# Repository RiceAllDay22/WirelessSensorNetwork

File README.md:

# Introduction to the Wireless Sensor Network Project
This repository contains the files utilized to create a low-cost wireless sensor network to identify, locate, and quantify CO2 sources within an area. The primary component of the network is the CO2 Sensor Node, for which there are two variants: the Arduino Version and the XBee Version. 

Both variants have the same essential function of collecting CO2 and wind data. The difference, however, is that the Arduino Version stores data within a microSD card, while the XBee Version sends data to a central hub. The XBee Version is the prominent hardware of this project.

An external repository called the [CSR_Arduino_Collection](https://github.com/RiceAllDay22/CSR_Arduino_Collection) is a complementary project that contains guides, codes, schematics, and datasheets for operating various sensors and modules, including the ones used in WSN. 

The overall WSN project is divided into three sections. [Section 1](https://github.com/RiceAllDay22/WirelessSensorNetwork/tree/master/Section1-Prototyping) focuses on the development of the Sensor Nodes. Next, [Section 2](https://github.com/RiceAllDay22/WirelessSensorNetwork/tree/master/Section2-Networking) establishes a wireless network between active nodes. Finally, [Section 3](https://github.com/RiceAllDay22/WirelessSensorNetwork/tree/master/Section3-Detecting) uses the collected data to identify and locate possible CO2 sources. Below are summaries and highlights of each section. 

# [Section 1: Developing the Sensor Nodes](https://github.com/RiceAllDay22/WirelessSensorNetwork/tree/master/Section1-Prototyping)
The Sensor Nodes are the backbone of WSN. Although there are two different variants: the Arduino Version and the XBee Version, they all consist of a CO2 sensor, a wind anemometer, and a time-keeping module.

[Arduino Version](https://github.com/jkub6/WirelessSensorNetwork/tree/master/Section1-ArduinoVersion) 
- Microcontroller is Arduino Nano
- Data saved on to a local microSD card
- Hardware is built on a solderless breadboard
- Code is compiled using Arduino IDE <br>

[XBee Version](https://github.com/jkub6/WirelessSensorNetwork/tree/master/Section2-XBeeVersion)
- Microcontroller is Digi XBee3
- Data transmitted to central hub
- Hardware is assembled on a custom printed-cicuit board
- Code is compiled using PyCharm

## Overview of Sensor Node
- [Arduino Version](https://github.com/RiceAllDay22/WirelessSensorNetwork/tree/master/Section1-Prototyping/SensorNode-ArduinoVersion)
- [XBee Version](https://github.com/RiceAllDay22/WirelessSensorNetwork/tree/master/Section1-Prototyping/SensorNode-XBeeVersion)

## Assessments of Individual Components
- [CU1106 CO2 Sensor](https://github.com/RiceAllDay22/WirelessSensorNetwork/tree/master/Section1-Prototyping/Assessment-CU1106) (not used for in current Node iterations)
- [SCD30 CO2 Sensor](https://github.com/RiceAllDay22/WirelessSensorNetwork/tree/master/Section1-Prototyping/Assessment-SCD30) (currently implemented in both Node versions)
- [DS3231 Timekeeping Module](https://github.com/RiceAllDay22/WirelessSensorNetwork/tree/master/Section1-Prototyping/Assessment-DS3231) (currently implemented in both Node versions)

## Power Evaluations
- [Power Usage of Nodes](https://github.com/RiceAllDay22/WirelessSensorNetwork/tree/master/Section1-Prototyping/Evaluation-PowerUsage)
- [Solar Requirement](https://github.com/RiceAllDay22/WirelessSensorNetwork/tree/master/Section1-Prototyping/Evaluation-PowerUsage)

# [Section 2: Establishing the Network](https://github.com/RiceAllDay22/WirelessSensorNetwork/tree/master/Section2-Networking)

The board is designed using Autodesk Eagle.

# [Section 3: Locating Possible Carbon Sources](https://github.com/RiceAllDay22/WirelessSensorNetwork/tree/master/Section3-Detecting)
## Node Software
Code controlling individual nodes is compiled through the Arduino IDE.

Arduino Library Requirments:
 - RTClib
 - SdFat

resources:
[One Drive Resources Folder](https://uofutah-my.sharepoint.com/:f:/g/personal/u1010401_umail_utah_edu/Ekx1kX9h63tNoVFmzbePeowB8LEIOgGHBQhFq369KU12vQ?e=vul3PO)

# Copyright and Contributors
Every hardware and every code in WirelessSensorNetwork and CSR_Arduino_Collection is given the Creative Commons License and the MIT License, respectively. Any content in the repository can be used and changed freely. The only requirement is that the original [license notice](https://github.com/jkub6/WirelessSensorNetwork/blob/master/LICENSE.md) is included in any copy of the software. 

The WirelessSensorNetwork project and the CSR_Arduino_Collection project are led by Adriann Liceralde under the leadership of Dr. Brian McPherson from the Carbon Science Research group at the University of Utah. Any questions, comments, or concerns are welcome to be sent to adriann8399@gmail.com.

Notable contributors to the project are Jacob Larkin, Charlie Leo, Tessa Bailey, Sean Taplin, and Andrew Winkelmann.

(c) Copyright 2022 Jacob Larkin and Adriann Liceralde

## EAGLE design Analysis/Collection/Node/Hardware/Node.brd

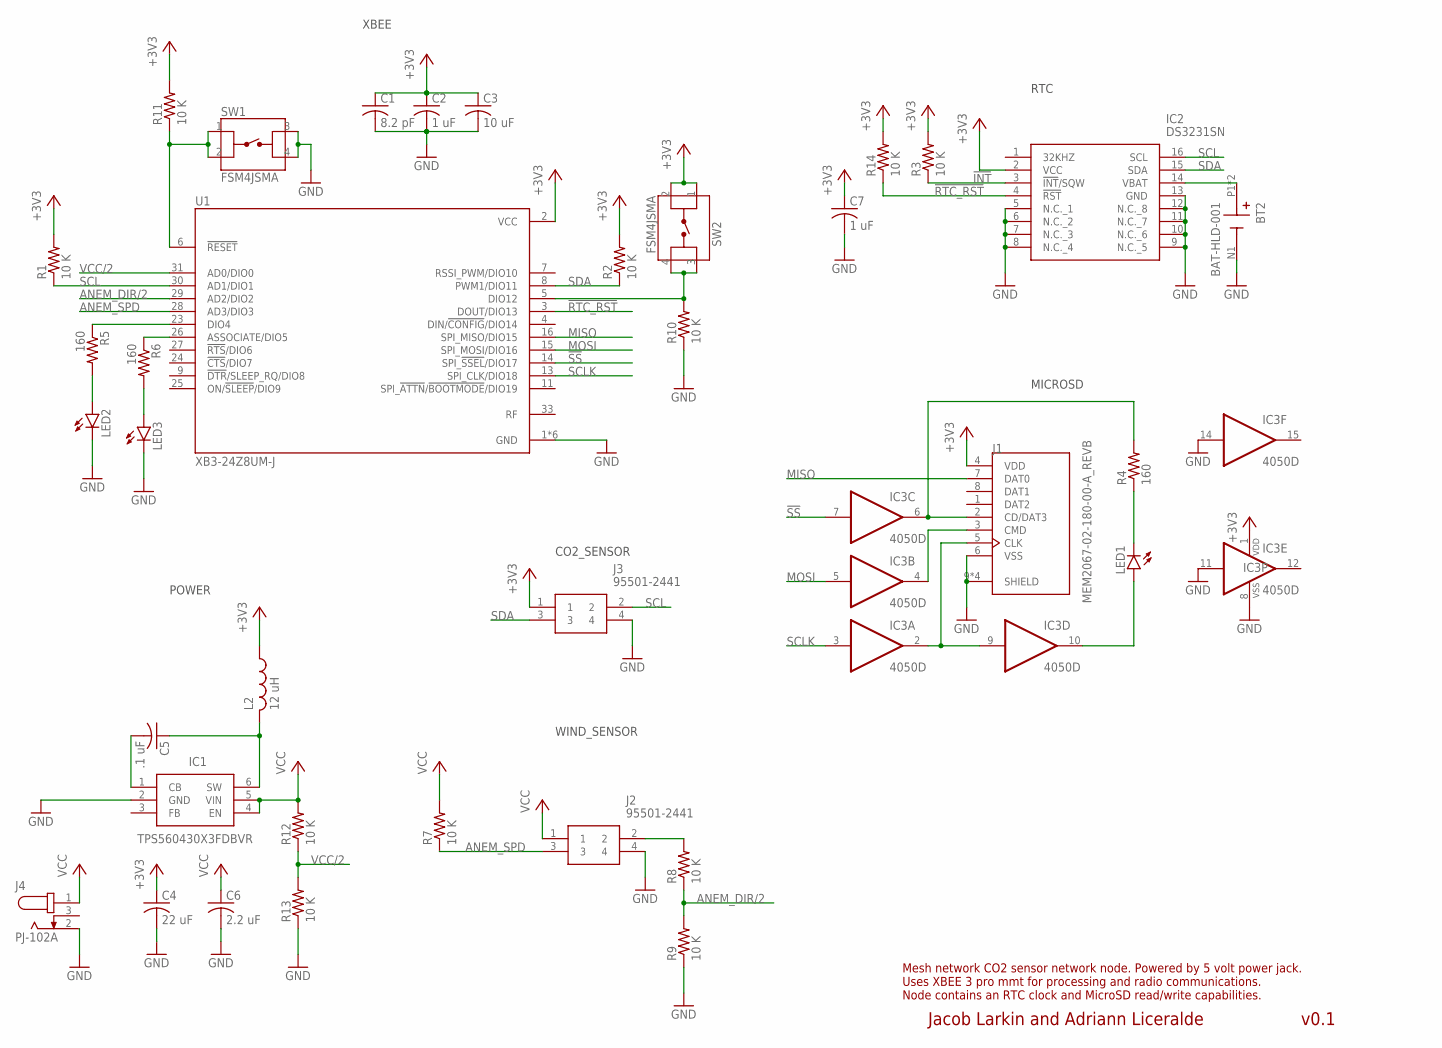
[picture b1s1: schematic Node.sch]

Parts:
BT2: BAT-HLD-001; BAT_BAT-HLD-001; MOUSER_NUM 712-BAT-HLD-001
C1: 8.2 pF; C0805; MOUSER_NUM 77-VJ0805A8R2BXXPBC
C2, C7: 1 uF; C0805; MOUSER_NUM 187-CL21B105KBFNNNG
C3: 10 uF; C0805; MOUSER_NUM 187-CL21A106KOQNNNG
C4: 22 uF; C0805; MOUSER_NUM 187-CL21A226MPQNNNE
C5: .1 uF; C0805; MOUSER_NUM 187-CL21B104KBCNNNC
C6: 2.2 uF; C0805; MOUSER_NUM 187-CL21A225KAFNNNE
IC1: TPS560430X3FDBVR; SOT95P280X145-6N; MOUSER_NUM 595-TPS560430X3FDBVR
IC2: DS3231SN; SOIC127P1032X265-16N; MOUSER_NUM 700-DS3231SN#T&R-
IC3: 4050D; SO16; MOUSER_NUM 771-74HC4050D-T
J1: MEM2067-02-180-00-A_REVB; GCT_MEM2067-02-180-00-A_REVB; DIGI-KEY_NUM 2073-MEM2067-02-180-00-ATR-ND
J2, J3: 95501-2441; 955012441; MOUSER_NUM 538-95501-2441
J4: PJ-102A; CUI_PJ-102A; MOUSER_NUM 490-PJ-102A
L2: 12 uH; L1812; MOUSER_NUM 652-CM453232-120KL
LED1, LED2, LED3: LEDCHIP-LED0805; CHIP-LED0805; MOUSER_NUM 720-LGR971-KN-1
R1, R2, R3, R7, R8, R9, R10, R11, R12, R13, R14: 10 K; R0805; MOUSER_NUM 660-RK73H2ATTD1002F
R4, R5, R6: 160; R0805; MOUSER_NUM 660-RK73H2ATTD1600F
SW1, SW2: FSM4JSMA; MOUSER_NUM 506-FSM4JSMA
U1: XB3-24Z8UM-J; XCVR_XB3-24Z8UM-J; MOUSER_NUM 888-XB3-24Z8UM

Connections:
!INT: IC2.3 (!INT!/SQW), R3.1
!RTC_RST: IC2.4 (!RST), R14.1, U1.3 (DOUT/DIO13)
!SS: IC3.7 (I), U1.14 (SPI_!SSEL!/DIO17)
+3V3: C1.1, C2.1, C3.1, C4.1, C7.1, IC2.2 (VCC), IC3.1 (VDD), J1.4 (VDD), J3.1, L2.1, R1.2, R2.2, R3.2, R11.2, R14.2, SW2.1, SW2.2, U1.2 (VCC)
ANEM_DIR: J2.2, R8.2
ANEM_DIR/2: R8.1, R9.2, U1.29 (AD2/DIO2)
ANEM_SPD: J2.3, R7.1, U1.28 (AD3/DIO3)
GND: BT2.N1 (-), C1.2, C2.2, C3.2, C4.2, C6.2, C7.2, IC1.2 (GND), IC2.5 (N.C._1), IC2.6 (N.C._2), IC2.7 (N.C._3), IC2.8 (N.C._4), IC2.9 (N.C._5), IC2.10 (N.C._6), IC2.11 (N.C._7), IC2.12 (N.C._8), IC2.13 (GND), IC3.8 (VSS), IC3.11 (I), IC3.14 (I), J1.6 (VSS), J1.9 (SHIELD), J1.10 (SHIELD), J1.11 (SHIELD), J1.12 (SHIELD), J2.4, J3.4, J4.2, LED2.C, LED3.C, R9.1, R10.1, R13.1, SW1.3, SW1.4, U1.1 (GND), U1.10 (GND), U1.12 (GND), U1.21 (GND), U1.32 (GND), U1.34 (GND)
MISO: J1.7 (DAT0), U1.16 (SPI_MISO/DIO15)
MOSI: IC3.5 (I), U1.15 (SPI_MOSI/DIO16)
unnamed: LED2.A, R5.2
unnamed: IC3.4 (O), J1.3 (CMD)
unnamed: C5.2, IC1.1 (CB)
unnamed: BT2.P1 (+), BT2.P2 (+), IC2.14 (VBAT)
unnamed: C5.1, IC1.6 (SW), L2.2
unnamed: IC3.6 (O), J1.2 (CD/DAT3), R4.2
unnamed: LED3.A, R6.2
unnamed: IC3.10 (O), LED1.A
unnamed: LED1.C, R4.1
unnamed: IC3.2 (O), IC3.9 (I), J1.5 (CLK)
unnamed: R5.1, U1.23 (DIO4)
unnamed: R6.1, U1.26 (ASSOCIATE/DIO5)
unnamed: R11.1, SW1.1, SW1.2, U1.6 (!RESET)
unnamed: R10.2, SW2.3, SW2.4, U1.5 (DIO12)
SCL: IC2.16 (SCL), J3.2, R1.1, U1.30 (AD1/DIO1)
SCLK: IC3.3 (I), U1.13 (SPI_CLK/DIO18)
SDA: IC2.15 (SDA), J3.3, R2.1, U1.8 (PWM1/DIO11)
VCC: C6.1, IC1.4 (EN), IC1.5 (VIN), J2.1, J4.1, R7.2, R12.2
VCC/2: R12.1, R13.2, U1.31 (AD0/DIO0)

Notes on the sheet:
Jacob Larkin and Adriann Liceralde
v0.1
Mesh network CO2 sensor network node. Powered by 5 volt power jack. Uses XBEE 3 pro mmt for processing and radio communications. Node contains an RTC clock and MicroSD read/write capabilities.
POWER
CO2_SENSOR
XBEE
RTC
MICROSD
WIND_SENSOR

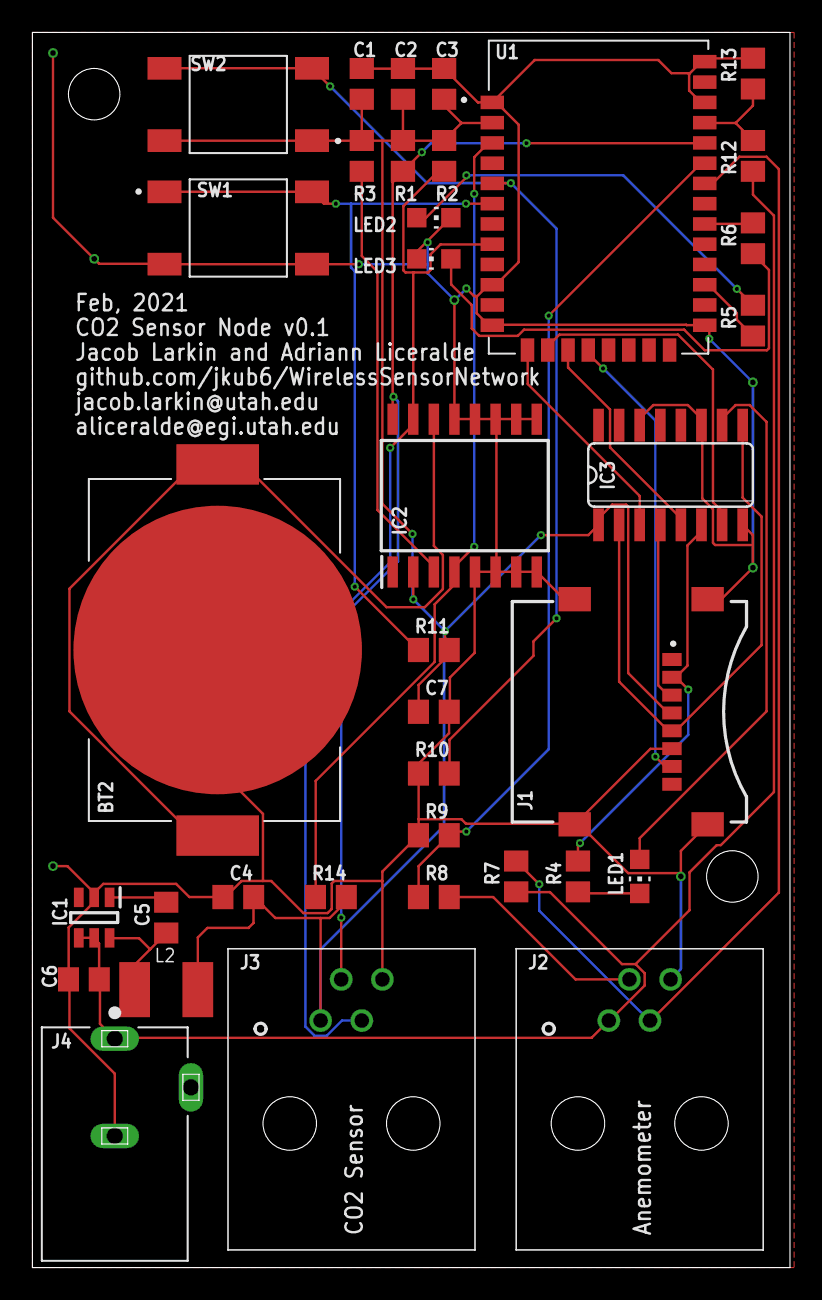
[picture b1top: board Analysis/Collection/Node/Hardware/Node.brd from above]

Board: 2 copper layers, 46.7 x 76.2 mm, 36 parts (0 on the bottom side), 29 nets.

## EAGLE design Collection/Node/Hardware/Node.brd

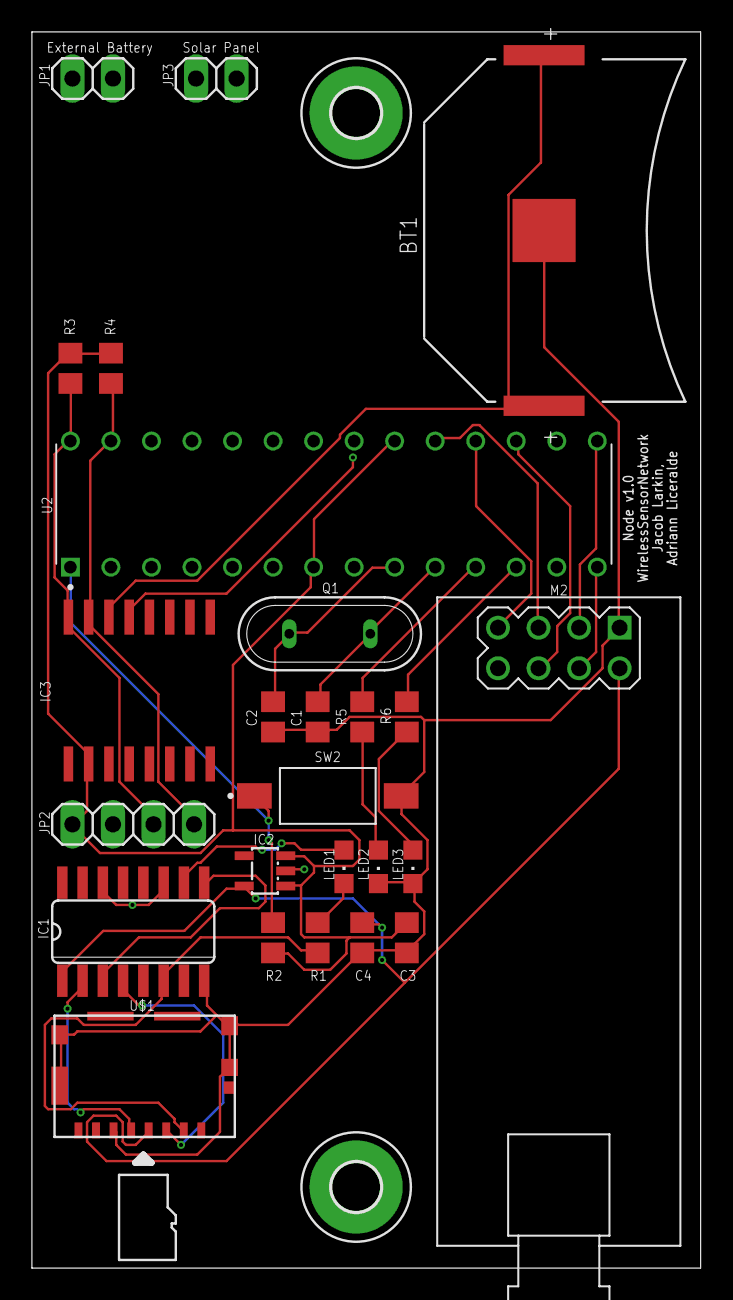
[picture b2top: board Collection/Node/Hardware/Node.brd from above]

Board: 2 copper layers, 41.9 x 77.5 mm, 27 parts (0 on the bottom side), 24 nets.

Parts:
BT1: KEYSTONE_ELECTRONICS_3034KEYSTONE_ELECTRONICS_303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; KEYSTONE_ELECTRONICS_3034_0
C1, C2: 22pF; C0805
C3, C4: .1uF; C0805
H1, H2: MOUNT-PAD-ROUND3.0; 3,0-PAD
IC1: 4050D; SO16
IC2: LP298XS; SOT23-5L
IC3: DS3231/SO; SO16W
JP1, JP3: 1X02
JP2: 1X04
LED1: RED; CHIPLED_0805
LED2: GREEN; CHIPLED_0805
LED3: Yellow; CHIPLED_0805
M2: WIRELESS-NRF24L01-PA-EXT
Q1: 16MHz; QS
R1, R5, R6: 1K; R0805
R2, R3, R4: 10K; R0805
SW2: FSMSM
U2: ATMEGA328P-PU; DIP-28
U$1: 1051620001A; 1051620001_SMT

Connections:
+3V3: C4.1, IC1.1, IC2.5, M2.2, U$1.4
+5V: C3.1, IC2.1, IC2.3, IC3.2, JP2.4, R2.2, R3.2, R4.2, U2.7, U2.20
CE: M2.3, U2.15
CLK: IC1.3, IC1.9
CSN: M2.4, U2.14
GND: BT1.1, C1.2, C2.2, C3.2, C4.2, IC1.8, IC1.11, IC1.14, IC2.2, IC3.13, JP1.2, JP2.3, JP3.2, LED2.C, LED3.C, M2.1, SW2.2, U2.8, U2.21, U2.22, U$1.6, U$1.G1, U$1.G2, U$1.G3, U$1.G4
MISO: M2.7, U2.18
MOSI: M2.6, U2.17
unnamed: IC1.10, LED1.A
unnamed: IC1.2, U$1.5
unnamed: IC1.6, R1.1, U$1.2
unnamed: LED1.C, R1.2
unnamed: IC1.4, U$1.3
unnamed: R2.1, SW2.1, U2.1
unnamed: C1.1, Q1.1, U2.10
unnamed: C2.1, Q1.2, U2.9
unnamed: R5.2, U2.11
unnamed: LED2.A, R5.1
unnamed: LED3.A, R6.1
unnamed: R6.2, U2.12
SCK: M2.5, U2.19
SCL: IC3.16, JP2.2, R3.1, U2.28
SDA: IC3.15, JP2.1, R4.1, U2.27
VBAT: BT1.2, BT1.2-2, IC3.14

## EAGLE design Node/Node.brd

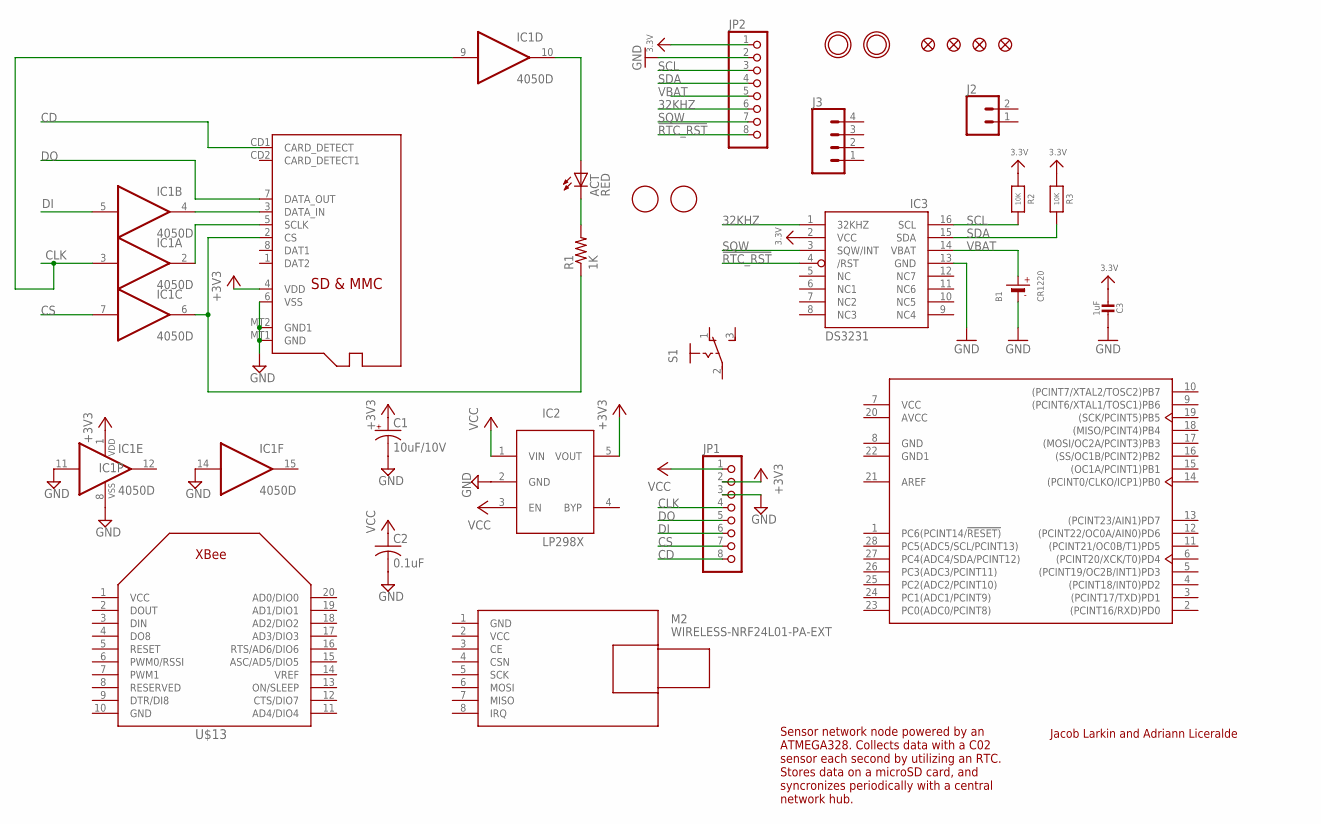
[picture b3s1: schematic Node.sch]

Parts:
ACT: RED; CHIP-LED0805
B1: CR1220
C1: 10uF/10V; A/3216-18R
C2: 0.1uF; C0805K
C3: 1uF; 0805-NO
FID1, FID2, FID3, FID4: FIDUCIAL""; FIDUCIAL_1MM
IC1: 4050D; SO16
IC2: LP298XS; SOT23-5L
IC3: DS3231/SO; SO16W
J2: CONN_02JST-PTH-2; JST-2-PTH
J3: CONN_04JST-PTH; JST-4-PTH
JP1: PINHD-1X8BIG; 1X08-BIG
JP2: HEADER-1X870MIL; 1X08_ROUND_70
M2: WIRELESS-NRF24L01-PA-EXT
R1: 1K; R0805
R2, R3: 10K; 0805-NO
S1: 255SB
U2: ATMEGA328P-PU; DIP-28
U$1, U$2: FIDUCIAL; FIDUCIAL_1MM
U$7, U$8: MOUNTINGHOLE2.5; MOUNTINGHOLE_2.5_PLATED
U$13: XBEE
X1: MICROSD

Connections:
3.3V: C3.2, IC3.2 (VCC), JP2.1, R2.1, R3.1
32KHZ: IC3.1 (32KHZ), JP2.6
!RTC_RST: IC3.4 (/RST), JP2.8
+3V3: C1.+, IC1.1 (VDD), IC2.5 (VOUT), JP1.2, X1.4 (VDD)
AVCC: U2.20 (AVCC)
CD: JP1.8, X1.CD1 (CARD_DETECT)
CLK: IC1.3 (I), IC1.9 (I), JP1.4
CS: IC1.7 (I), JP1.7
DI: IC1.5 (I), JP1.6
DO: JP1.5, X1.7 (DATA_OUT)
GND_RTC: B1.-, C3.1, IC3.13 (GND), JP2.2
GND_SD: C1.-, C2.2, IC1.8 (VSS), IC1.11 (I), IC1.14 (I), IC2.2 (GND), JP1.3, M2.1 (GND), U2.8 (GND), U2.22 (GND1), X1.6 (VSS), X1.MT1 (GND), X1.MT2 (GND1)
unnamed: ACT.A, IC1.10 (O)
unnamed: IC1.2 (O), X1.5 (SCLK)
unnamed: IC1.6 (O), R1.1, X1.2 (CS)
unnamed: ACT.C, R1.2
unnamed: IC1.4 (O), X1.3 (DATA_IN)
SCL: IC3.16 (SCL), JP2.3, R2.2
SDA: IC3.15 (SDA), JP2.4, R3.2
SQW: IC3.3 (SQW/INT), JP2.7
VBAT: B1.+$1 (+), IC3.14 (VBAT), JP2.5
VCC_SD: C2.1, IC2.1 (VIN), IC2.3 (EN), JP1.1, M2.2 (VCC), U2.7 (VCC)

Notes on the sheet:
Jacob Larkin and Adriann Liceralde
Sensor network node powered by an ATMEGA328. Collects data with a C02 sensor each second by utilizing an RTC. Stores data on a microSD card, and syncronizes periodically with a central network hub.

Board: 2 copper layers, 28 parts (0 on the bottom side), 21 nets, no tracks yet.

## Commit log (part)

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2020-03-05 move pipfile
2020-03-05 moved file
2020-03-06 added random message
2020-03-06 Removed tests
2020-03-06 Organizating Folders
2020-03-08 Added Version 1 Data sets
2020-03-08 Added data sets
2020-03-08 Added Bunch of Arduino Files
2020-03-08 Test second comp
2020-03-09 Added new data and fixing Analyzer code
2020-03-09 Add test file
2020-03-09 more test
2020-03-09 mpre test
2020-03-09 push agai
2020-03-09 test
2020-03-09 pull test
2020-03-09 Updated schematic
2020-03-10 Improved frame selector
2020-03-11 Adjusted board size
2020-03-22 Analyzer code update
2020-03-22 Removed outdated analyzer versions
2020-03-22 Created ASCI Combiner
2020-03-22 Remove Old CSV Combiner
2020-03-22 Combiner for both ASCI and Binary are operational
2020-03-22 Fixed Full Main Analyzer
2020-03-22 Removed unneccesary files
2020-03-22 Analyzer optimization
2020-03-23 Analyzer optimizing
2020-03-23 Analyzer step 2 for 3 node test
2020-03-24 Bump bleach from 3.1.1 to 3.1.2
    Bumps [bleach](https://github.com/mozilla/bleach) from 3.1.1 to 3.1.2.
    - [Release notes](https://github.com/mozilla/bleach/releases)
    - [Changelog](https://github.com/mozilla/bleach/blob/master/CHANGES)
    - [Commits](https://github.com/mozilla/bleach/compare/v3.1.1...v3.1.2)
2020-03-25 Analyzer Step 2
2020-03-27 Old data
2020-03-31 Bump bleach from 3.1.1 to 3.1.4
    Bumps [bleach](https://github.com/mozilla/bleach) from 3.1.1 to 3.1.4.
    - [Release notes](https://github.com/mozilla/bleach/releases)
    - [Changelog](https://github.com/mozilla/bleach/blob/master/CHANGES)
    - [Commits](https://github.com/mozilla/bleach/compare/v3.1.1...v3.1.4)
2020-04-09 testing new comp
2020-04-09 Test pull
2020-04-29 Test2
2020-04-29 Test3
2020-04-29 Test5
2020-04-29 Test6?
2020-04-29 Test6.5
2020-04-29 Remove Arduino
2020-04-29 Test Arduino Folder
2020-04-29 Change sketch using Arduino IDE
2020-04-29 Test Arduino IDE and Git together
2020-04-29 Add Serial
2020-04-29 test arduino
2020-04-29 more testing
2020-04-29 Simplified Serial
2020-04-29 Removed unnecessary files
2020-04-29 Added Arduino codes
2020-04-29 Organized Collection Folder
2020-04-29 Edit Continuous Codes
2020-04-30 Changes to FastClock File
2020-04-30 Little changes
2020-04-30 Added libraries
2020-04-30 Implement Improved SD card to Continuous Min
2020-04-30 Continuous Collection edit
2020-04-30 Add new data
2020-04-30 Enhance codes
2020-05-01 Test Binary Data
2020-05-01 Attempt binary
2020-05-02 New Arduino XBee Code that works
2020-05-02 Update code
2020-05-02 SD Card Reader
2020-05-03 Xbee Transmitting mini csv file success
2020-05-03 Update xbee code
2020-05-03 bi-directional xbee communication
2020-05-03 small change xbee
2020-05-04 organize files
2020-05-04 edit xbee codes
2020-05-04 Xbee Range
2020-05-04 edit
2020-05-05 xbee edit
2020-05-05 Xbee A
2020-05-08 test edit
2020-05-08 testing git
2020-05-13 Restructured to allow support for packages, platformio, unit tests, libraries, spike directories, workspaces, and microcontroller simulation. Implemented CRC32 in C++ and Python
2020-05-13 added blink unit test, re-added software_old
2020-05-13 added debug config, controller begin methods, mode selection enums
2020-05-14 crc32 unit tests, testing github remote test workflow
2020-05-14 testing github remote test workflow #2
2020-05-14 testing github remote test workflow #3
2020-05-14 testing github remote test workflow #4
2020-05-14 testing github remote test workflow #5
2020-05-14 testing github remote test workflow #6
2020-05-14 testing github remote test workflow #7
2020-05-14 testing github remote test workflow #8
2020-05-14 testing github remote test workflow #9
2020-05-14 testing github remote test workflow #10
2020-05-14 testing github remote test workflow #11
2020-05-14 testing github remote test workflow #12
2020-05-14 testing github remote test workflow #13
2020-05-15 Added simulation controllers, rolling crc32 in sd
2020-05-16 optimized storage, added c02 sensor
2020-05-16 check
2020-05-18 added csv and binary capabilities to data_utils.py. Made many unit tests.
2020-05-19 basic checksum test for binary file creation
2020-05-20 added node output file merging and respective unit tests
2020-05-20 remove pipfile.lock, fix for cross-platform cartopy
2020-05-20 Added windows cartopy workaround to pipfile
2020-05-20 added shared-wheels folder to git
2020-05-20 added proj and geos to unittest dependencies
2020-05-20 changed proj to libproj-dev
2020-05-20 changed geos to libgeos-dev
2020-05-21 forced pandas to use little-endian byte ordering
2020-05-21 changed merge unit test hash algorithm
2020-05-21 added debugging print statment
2020-05-21 sort dataframe prior to hashing for unit test
2020-05-21 re-added debug statment
2020-05-21 reindexed DataFrame after sorting
2020-05-21 attempt to get pip cache working
2020-05-21 added sphynx
2020-05-21 renamed doc to docs
2020-05-21 Set theme jekyll-theme-tactile
2020-05-21 Create CNAME
2020-05-23 added valid and invalid unit tests for merge files
2020-05-23 created test visualization python notebook
2020-05-25 added visualization tests
2020-05-25 removed bad dependency
2020-06-11 USB Meter Logger
2020-06-12 Added data
2020-06-14 Basic clink changes
2020-06-17 USB Code
2020-06-17 USB code changes
2020-06-17 edit USB code
2020-06-20 Continous code, minor edits
2020-06-22 New data
2020-06-23 Binary file complete
2020-06-23 Binary csv reader
2020-06-24 Edit binary translater
2020-06-29 Power consumption stuff
2020-07-02 Edited something
2020-07-02 Edit Arduino test code
2020-07-03 Edit Analyzer
2020-07-06 Edit Continuous Code
2020-07-07 wind code
2020-07-07 Add solar production data
2020-07-08 Wind sensor code
2020-07-09 Fixed USBLogger code
2020-07-12 Added wind columns for analysis
2020-07-13 Continuous Code Version 4
2020-07-14 real data
2020-07-14 stuff
2020-07-15 Added LCD to continuous 4
2020-07-15 Collection Version 5
2020-07-15 Continuous V5 for 5 second intervals
2020-07-18 Davis Anemometer code
2020-07-20 Continuous Version 6
2020-07-20 Simple fix
2020-07-21 Added RStudio Files
2020-07-27 XBee One-way transmission
2020-07-28 XBee code
2020-07-28 Continuous Version 7
2020-08-11 Arduino XBee Test
2020-08-12 Continuous Version 8
2020-08-12 Arduino Xbee Decoder
2020-08-15 Misc organization
2020-08-31 Continuous 9
2020-08-31 Remove SD Reset
2020-09-04 Continuous 9 Edit rtc
2021-01-31 Continuous Version 10
2021-01-31 File Reader
2021-01-31 Add Lego Home Test Data
2021-01-31 Move Continuous10
2021-02-16 Redesigned Hardware
2021-02-18 Update File Reader
2021-05-24 Continuous Version 11
2021-05-26 Continuous 11
2021-06-08 SCD30 Codes
2021-06-15 Test code for SCD30 frequency
2021-06-17 test git
2021-06-22 openair R
2021-06-22 RTC TimeDrift Test
2021-06-23 openair setup for analyzing data
2021-06-24 openair analysis
2021-06-29 Continuous 11 for Union Deployment
2021-06-29 Continuous Beta 11
2021-06-30 SCD30 Sensor Code
2021-06-30 Continus 11 added calibration
2021-07-04 PWM rough code for MH-Z16
2021-07-06 Union Deployment Prep
2021-07-12 Continuous Code Version 12
2021-07-12 Added Union Data
2021-07-13 NEw Binary Combine
2021-07-13 Binary Code and R Code
2021-07-16 Openair
2021-07-16 Test Data
2021-07-16 continuous 12 Version B
2021-07-18 V2.6 Data
2021-08-04 Establish PyCharm directory
2021-08-06 PyCharm
2021-08-07 New Node
2021-08-14 Digi and Arduino
2021-08-18 many
2021-08-19 Union Roof Prep with enhanced Arduino Nodes
2021-08-20 8-19-21 Added Primary Node Data
2021-08-20 Added 8-19 Secondary Node's Data
2021-08-23 Data Processing
2021-08-24 Data Analysis for Update
2021-08-26 Remove test
2021-08-26 Remove uncessary Pycharm Projects
2021-09-06 Arduino, PyCharm, etc.
2021-09-11 Remove some PyCharm projects
2021-09-11 Import Digi Samples
2021-09-13 Watch Dog, More Sample Tests
2021-09-21 Multi SCD
2021-10-25 10-24-21 Crisis Mode Updates
2021-10-26 10-26-21
2021-11-12 Showcase Prep
2021-11-17 Files cleanup
2021-11-26 11-24 Lab Idle Data
2021-11-28 PyCharm Node Bytes Transmission
2021-11-28 Fram and Main
2021-11-29 Fram
2022-01-04 File Transfer
2022-01-11 ArduinoBoard
2022-01-12 Organize Python
2022-01-13 Continuous14
2022-01-15 Dual Serial Line for Central
2022-01-16 CentralHub Broadcast
2022-01-16 PyCharm Digi Fix Test
2022-01-16 PyCharm Digi Fix
2022-01-16 Change BaseTest9
2022-01-16 BaseTest10
2022-01-16 Check BaseTest9 again
2022-01-17 Github test for PyCharm Digi
2022-01-17 Test github
2022-01-17 Test 17 and 18
2022-01-17 BaseTest19and20
2022-01-17 Base Test 21 and 22
2022-01-17 BaseTests
2022-01-17 Base Tests
2022-01-17 All successful
2022-01-17 check BaseTest changes
2022-01-17 Check all BaseTests 17 to 22
2022-01-18 PyCharm cleanup
2022-01-18 Reorganize Digi Samples
2022-01-18 PyCharm Project Revivals
2022-01-18 Upload Laptop2 PyCharm projects
2022-01-18 PyCharm Subfolder Organization
2022-01-20 PyCharm MainCode and FramStorage
2022-01-22 Fram Code
2022-01-23 CU-1106 Analysis
2022-01-25 Fram Emergency
2022-01-27 Error Fixes
2022-02-03 OAT test
2022-02-08 Restore Node Folder
2022-02-10 CentralHub
2022-02-15 PCBv2
2022-02-18 File Removal
2022-03-01 Rename README.md to README_original.md
2022-03-06 Reorganize Repo
2022-03-16 Readme
2022-03-17 ArduinoVersion guide
2022-03-18 Organize Folders structure
2022-03-18 Completed ArduinoVersion SensorNode
2022-03-18 Transferred SCD30 Assessment Files
2022-03-19 Completed and Transferred RTC Assessment
2022-03-20 MultiRTC
2022-03-20 Completed and Added CU1106 Assessment
2022-03-23 Completed and added PowerUsage
2022-03-24 Completed and added Solar Requirement
2022-04-19 CentralHub Code
2022-06-14 Added README
2022-06-22 Anti-error code in MainCode
2022-06-23 Test New Link Commit
2022-06-23 Slight changes to MainCode
2024-11-19 Bump wheel from 0.34.2 to 0.38.1 in /UnusedFiles/JacobFiles/OldlPython
    Bumps [wheel](https://github.com/pypa/wheel) from 0.34.2 to 0.38.1.
    - [Release notes](https://github.com/pypa/wheel/releases)
    - [Changelog](https://github.com/pypa/wheel/blob/main/docs/news.rst)
    - [Commits](https://github.com/pypa/wheel/compare/0.34.2...0.38.1)
    ---
    updated-dependencies:

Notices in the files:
parts and their libraries:
diy-modules: Released under the Creative Commons Attribution 4.0 International License: http://creativecommons.org/licenses/by/4.0
microbuilder: This work is placed in the public domain, and may be freely used for commercial and non-commercial work with the following conditions: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
